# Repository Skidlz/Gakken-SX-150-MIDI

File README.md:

This project adds MIDI support to the Gakken SX-150 mk II using an Arduino R4.

This includes CCs for all original controls, plus additional parameters.

## Additional Hardware Features:
- Sustain and Release Stages (for existing hardware envelope)
- Inverted Envelope Mode
- Pulse, Dual Pulse, Super Saw, and other Waveforms
- Pulse Width Modulation
- Square and Triangle Sub Oscillators
- VCF Drive adjustment
- Envelope to VCF Depth Adjustment
- High Pass Filter Mode
- LFO to VCF Modulation
- Improved LFO sync
- VCA
- LED indicators for LFO and Envelope

## Additional Software Features:
 - Extra Software Envelopes with S/H
 - Extra Software LFOs
 - Pitch Bend
 - Portamento
 - Legato
 - Velocity-triggered Accent
 - Velocity Modulation
 - VCF Keytracking
 - Delay and Fade-in for Hardware LFO
 - Quantizing for Touchstrip

## Routing Diagram

## Schematic Diagram

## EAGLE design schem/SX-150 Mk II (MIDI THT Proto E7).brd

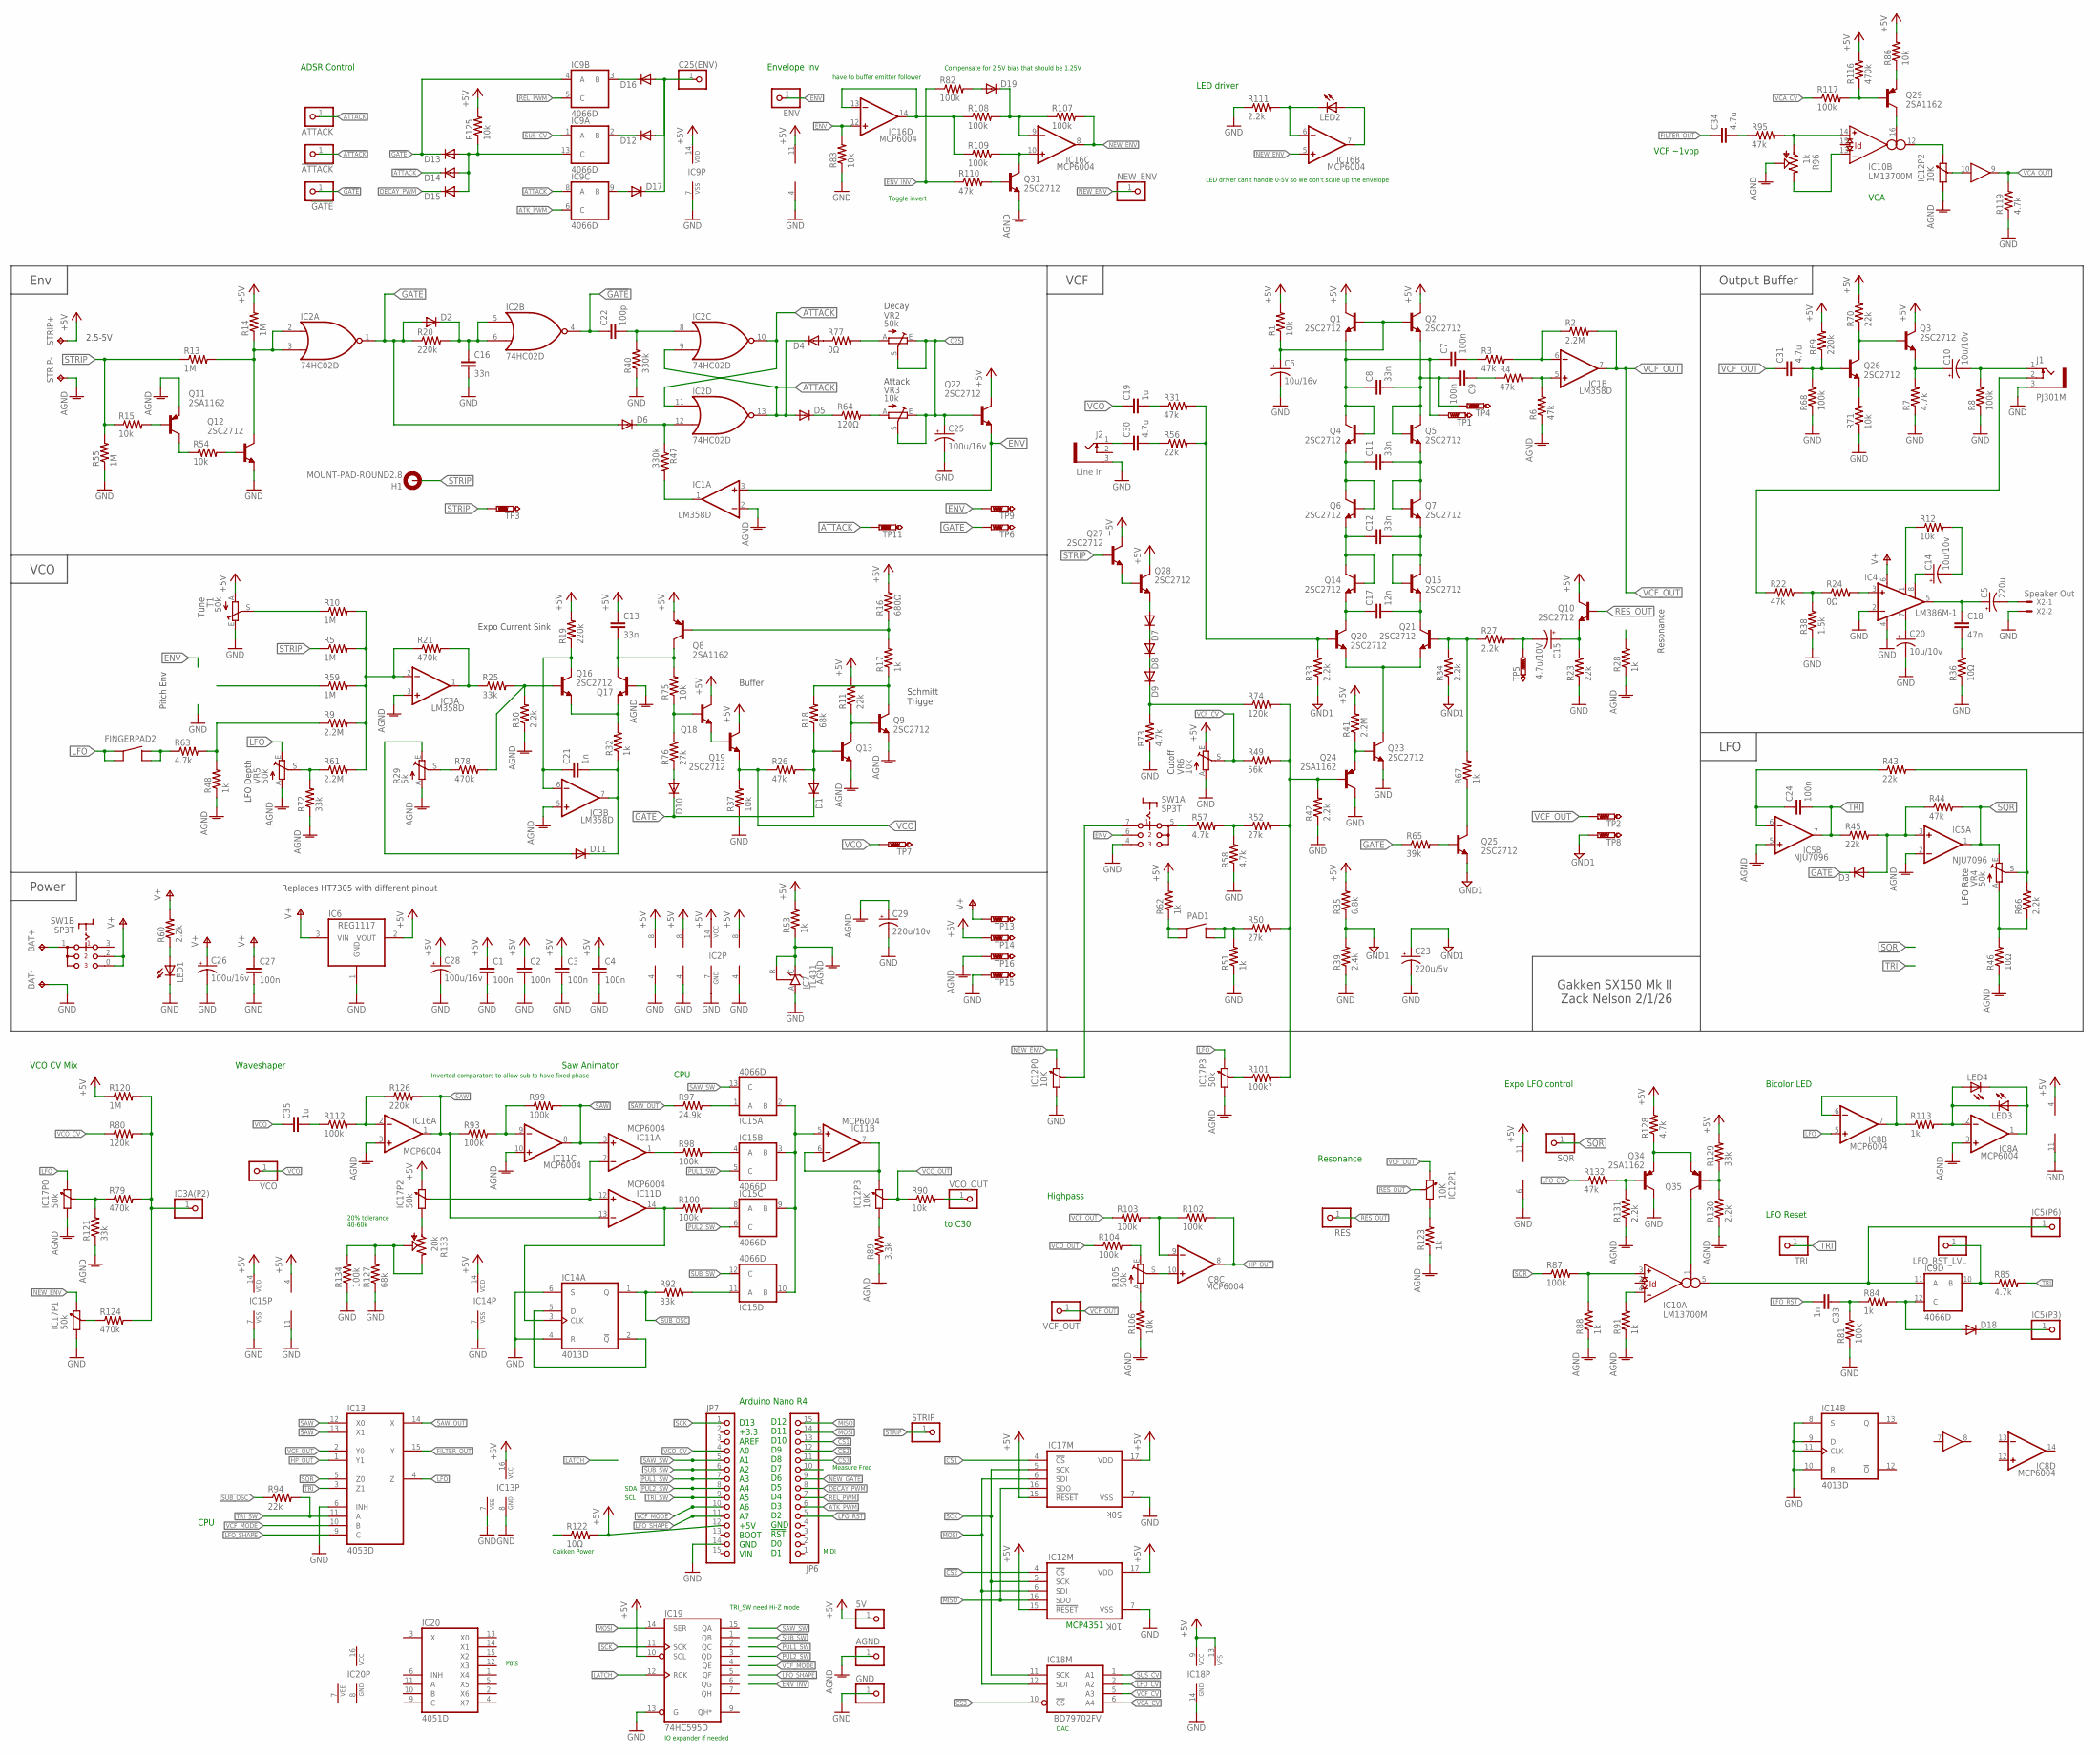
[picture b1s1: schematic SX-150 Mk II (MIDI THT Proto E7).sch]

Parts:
5V: PINHD-1X1; 1X01
!ATTACK: PINHD-1X1; 1X01
!GATE: PINHD-1X1; 1X01
AGND: PINHD-1X1; 1X01
ATTACK: PINHD-1X1; 1X01
BAT+: TPPAD1-13; P1-13
BAT-: TPPAD1-13; P1-13
C1, C2, C3, C4, C7, C9, C24, C27: 100n; C0603
C5: 220u; E2,5-6
C6: 10u/16v; E2,5-6
C8, C11, C12, C13, C16: 33n; C0603
C10, C14, C20: 10u/10v; E2,5-6
C15: 4.7u/10V; E2,5-6
C17: 12n; C0603
C18: 47n; C0603
C19, C35: 1u; C0603
C21, C33: 1n; C0603
C22: 100p; C0603
C23: 220u/5v; E2,5-6
C25, C26, C28: 100u/16v; E2,5-6
C25(ENV): PINHD-1X1; 1X01
C29: 220u/10v; E2,5-6
C30, C31, C34: 4.7u; C0603
D1, D10, D11: DIODE-DO41-7.6; DO41-7.6
D2, D3, D4, D5, D6, D7, D8, D9, D12, D13, D14, D15, D16, D17, D18, D19: DIODE-MINIMELF; MINIMELF
ENV: PINHD-1X1; 1X01
FINGERPAD2: GAKKEN-PAD
GND: PINHD-1X1; 1X01
H1: MOUNT-PAD-ROUND2.8; 2,8-PAD
IC1, IC3: LM358D; SO08
IC2: 74HC02D; SO14
IC3A(P2), IC5(P3), IC5(P6): PINHD-1X1; 1X01
IC4: LM386M-1; SO08
IC5: NJU7096; SO08
IC6: REG1117; SOT223
IC7: TL431; TO92-CLP
IC8, IC11, IC16: MCP6004; SO14
IC9, IC15: 4066D; SO14
IC10: LM13700M; SO16
IC12: 10K; TSSOP20_MC_MCH
IC13: 4053D; SO16
IC14: 4013D; SO14
IC17: 50k; TSSOP20_MC_MCH
IC18: BD79702FV; TSSOP14
IC19: 74HC595D; SO16
IC20: 4051D; SO16
J1: PJ301M; JACK-3.5-NOHOLE
J2: Line In; JACK-3.5-NOHOLE
JP6, JP7: PINHD-1X15; 1X15
LED1, LED2, LED3, LED4: LED3MM
LFO_RST_LVL: PINHD-1X1; 1X01
NEW_ENV: PINHD-1X1; 1X01
PAD1: GAKKEN-PAD
Q1, Q2, Q3, Q4, Q5, Q6, Q7, Q9, Q10, Q12, Q13, Q14, Q15, Q16, Q17, Q18, Q19, Q20, Q21, Q22, Q23, Q25, Q26, Q27, Q28, Q31: 2SC2712; SOT23-BEC
Q8, Q11, Q24, Q29, Q34, Q35: 2SA1162; SOT23-BEC
R1, R12, R15, R37, R54, R71, R75, R83, R86, R90, R106, R125: 10k; R0603
R2, R9, R41, R61: 2.2M; R0603
R3, R4, R6, R22, R26, R31, R44, R95, R110, R132: 47k; R0603
R5, R10, R13, R14, R55, R59, R120: 1M; R0603
R7, R57, R58, R63, R73, R85, R119, R128: 4.7k; R0603
R8, R68, R81, R82, R87, R93, R98, R99, R100, R102, R103, R104, R107, R108, R109, R112, R117, R134: 100k; R0603
R11, R23, R43, R45, R56, R70, R94: 22k; R0603
R16: 680Ω; R0603
R17, R28, R32, R48, R51, R53, R62, R67, R84, R88, R91, R113, R123: 1k; R0603
R18, R127: 68k; R0603
R19, R20, R69, R126: 220k; R0603
R21, R78, R79, R116, R124: 470k; R0603
R24, R77: 0Ω; R0603
R25, R72, R92, R121, R129: 33k; R0603
R27, R30, R33, R34, R42, R60, R66, R111, R130, R131: 2.2k; R0603
R29: 5k; B25P
R35: 6.8k; R0603
R36, R46, R122: 10Ω; R0603
R38: 1.5k; R0603
R39: 2.4k; R0603
R40, R47: 330k; R0603
R49: 56k; R0603
R50, R52, R76: 27k; R0603
R64: 120Ω; R0603
R65: 39k; R0603
R74, R80: 120k; R0603
R89: 3.3k; R0603
R96: 1k; B25P
R97: 24.9k; R0603
R101: 100k?; R0603
R105: 50k; B25P
R133: 20k; B25P
RES: PINHD-1X1; 1X01
SQR: PINHD-1X1; 1X01
STRIP: PINHD-1X1; 1X01
STRIP+: TPB2,54; B2,54
STRIP-: TPB2,54; B2,54
SW1: SP3T
T1: 50k; CA9V
TP1, TP2, TP3, TP4, TP5, TP6, TP7, TP8, TP9, TP11, TP13, TP14, TP15, TP16: PTR1B1,27; B1,27
TRI: PINHD-1X1; 1X01
VCF_OUT: PINHD-1X1; 1X01
VCO: PINHD-1X1; 1X01
VCO_OUT: PINHD-1X1; 1X01
VR2, VR4, VR5: 50k; CA9V
VR3, VR6: 10k; CA9V
X2: Speaker Out; 22-23-2021

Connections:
!ATTACK: !ATTACK.1, D14.C, IC2.10 (O), IC2.11 (I0)
!CS1: IC17.4 (!CS), JP6.13
!CS2: IC12.4 (!CS), JP6.12
!CS3: IC18.10 (!CS), JP6.11
!GATE: !GATE.1, C22.1, D1.C, D3.C, D10.C, D13.C, IC2.4 (O), IC9.4 (A)
!SAW: IC11.3 (+IN), IC11.8 (OUT), IC13.13 (X1), R99.2
+5V: 5V.1, C1.1, C2.1, C3.1, C4.1, C13.1, C28.+, IC1.8 (V+), IC2.14 (VCC), IC3.8 (V+), IC5.8 (V+), IC6.2 (VOUT), IC8.4 (V+), IC9.14 (VDD), IC10.11 (V+), IC11.4 (V+), IC12.15 (!RESET), IC12.17 (VDD), IC13.16 (VCC), IC14.14 (VDD), IC15.14 (VDD), IC16.11 (V-), IC17.15 (!RESET), IC17.17 (VDD), IC17.18 (B), IC18.9 (VCC), IC18.13 (VFS), IC19.10 (SCL), JP7.12, Q1.C, Q2.C, Q3.C, Q8.E, Q10.C, Q18.C, Q19.C, Q22.C, Q27.C, Q28.C, R1.2, R11.2, R14.2, R16.2, R19.2, R35.2, R41.2, R53.2, R62.2, R69.2, R70.2, R86.2, R116.2, R120.1, R122.2, R125.2, R128.2, R129.2, STRIP+.TP, T1.A, TP14.TP, VR6.E
AGND: AGND.1, C29.+, IC1.2 (-IN), IC3.3 (+IN), IC3.5 (+IN), IC5.2 (-IN), IC5.5 (+IN), IC7.C, IC7.R, IC8.3 (+IN), IC11.10 (+IN), IC12.20 (A), IC16.3 (+IN), IC17.1 (A), IC17.11 (A), Q9.E, Q11.E, Q13.E, Q17.B, Q31.E, R6.1, R28.1, R29.A, R30.1, R46.1, R48.1, R53.1, R72.1, R88.1, R89.1, R91.1, R96.S, R106.1, R121.1, R123.1, R130.1, R131.1, STRIP-.TP, TP16.TP, VR5.A
ATK_PWM: IC9.6 (C), JP6.6
ATTACK: ATTACK.1, D4.C, D5.A, IC2.9 (I1), IC2.13 (O), IC9.8 (A), TP11.TP
C25: C25.+, C25(ENV).1, D12.A, D16.A, D17.C, Q22.B, VR2.E, VR2.S, VR3.E, VR3.S
DECAY_PWM: D15.C, JP6.8
ENV: ENV.1, IC1.3 (+IN), IC16.12 (+IN), Q22.E, R83.2, SW1.6 (T2), TP9.TP
ENV_INV: R82.1, R110.1
FILTER_OUT: C34.1, IC13.15 (Y)
GATE: D2.A, D6.A, IC2.1 (O), R20.1, R65.1, TP6.TP
GND: BAT-.TP, C1.2, C2.2, C3.2, C4.2, C6.-, C16.2, C20.-, C23.-, C25.-, C26.-, C27.2, C28.-, C29.-, GND.1, IC1.4 (V-), IC2.7 (GND), IC3.4 (V-), IC4.2 (-IN), IC4.4 (GND), IC5.4 (V-), IC6.1 (GND), IC7.A, IC8.11 (V-), IC9.7 (VSS), IC10.6 (V-), IC11.11 (V-), IC12.7 (VSS), IC12.11 (A), IC13.6 (INH), IC13.7 (VEE), IC13.8 (GND), IC14.4 (R), IC14.6 (S), IC14.7 (VSS), IC14.8 (S), IC14.9 (D), IC14.10 (R), IC14.11 (CLK), IC15.7 (VSS), IC16.4 (V+), IC17.7 (VSS), IC17.10 (A), IC18.14 (GND), IC19.8 (GND), IC19.13 (G), IC20.8 (GND), J1.3 (1), J2.3 (1), JP7.14, LED1.K (C), Q12.E, Q23.E, Q24.C, Q34.C, R7.1, R8.1, R23.1, R36.1, R37.1, R38.1, R39.1, R40.1, R42.1, R51.1, R55.1, R58.1, R68.1, R71.1, R73.1, R81.1, R83.1, R111.1, R119.1, R127.1, R134.1, SW1.4 (T3), T1.E, TP15.TP, VR6.A, X2.2
GND1: C23.+, Q25.E, R33.1, R34.1, R35.1, R39.2, TP8.TP
HP_OUT: IC8.8 (OUT), IC13.1 (Y1), R102.2
LATCH: IC19.12 (RCK)
LFO: FINGERPAD2.A0, FINGERPAD2.A1, IC8.5 (+IN), IC13.4 (Z), IC17.3 (B), IC17.13 (B), VR5.E
LFO_CV: IC18.2 (A2), R132.1
LFO_RST: C33.2, JP6.5
LFO_SHAPE: IC13.9 (C), JP7.11
MISO: IC12.16 (SDO), IC17.16 (SDO), JP6.15
MOSI: IC12.6 (SDI), IC17.6 (SDI), IC18.12 (SDI), IC19.14 (SER), JP6.14
unnamed: IC1.1 (OUT), R47.2
unnamed: D5.C, R64.1
unnamed: IC2.2 (I0), IC2.3 (I1), Q12.C, R13.2, R14.1
unnamed: D12.C, IC9.2 (B)
unnamed: C22.2, IC2.8 (I0), R40.2
unnamed: Q12.B, R54.2
unnamed: C16.1, D2.C, IC2.5 (I0), IC2.6 (I1), R20.2
unnamed: D6.C, IC2.12 (I1), R47.1
unnamed: D4.A, R77.1
unnamed: D17.A, IC9.9 (B)
unnamed: R64.2, VR3.A
unnamed: D19.A, R82.2
unnamed: Q11.C, R54.1
unnamed: Q11.B, R15.2
unnamed: R61.1, R72.2, VR5.S
unnamed: IC5(P6).1, IC9.11 (A), IC10.5 (OUT)
unnamed: IC3.2 (-IN), R5.2, R9.2, R10.2, R21.1, R59.2, R61.2
unnamed: D18.C, IC5(P3).1
unnamed: R46.2, R66.1, VR4.A
unnamed: R43.2, R66.2, VR4.S
unnamed: IC3.1 (OUT), R21.2, R25.1
unnamed: Q16.B, R25.2, R30.2, R78.2
unnamed: R9.1, R48.2, R63.2
unnamed: R10.1, T1.S
unnamed: C13.2, Q8.C, Q17.C, R75.2
unnamed: Q8.B, R16.1, R17.2
unnamed: C21.2, D11.C, IC3.7 (OUT), R32.1
unnamed: Q16.E, Q17.E, R32.2
unnamed: C21.1, IC3.6 (-IN), Q16.C, R19.1
unnamed: Q9.C, R17.1, R18.2
unnamed: Q18.B, R75.1, R76.2
unnamed: Q18.E, Q19.B
unnamed: BAT+.TP, SW1.1
unnamed: Q9.B, Q13.C, R11.1
unnamed: D1.A, Q13.B, R18.1, R26.2
unnamed: D10.A, R76.1
unnamed: C7.1, C8.1, Q1.E, Q4.B, Q4.C, TP1.TP
unnamed: C8.2, C9.2, Q2.E, Q5.B, Q5.C, TP4.TP
unnamed: C6.+, Q1.B, Q2.B, R1.1
unnamed: Q20.E, Q21.E, Q23.C
unnamed: C11.1, Q4.E, Q6.B, Q6.C
unnamed: C11.2, Q5.E, Q7.B, Q7.C
unnamed: Q20.B, R31.2, R33.2, R56.2
unnamed: C12.1, Q6.E, Q14.B, Q14.C
unnamed: C12.2, Q7.E, Q15.B, Q15.C
unnamed: C17.1, Q14.E, Q20.C
unnamed: C17.2, Q15.E, Q21.C
unnamed: Q21.B, R27.1, R34.2, R67.2
unnamed: C7.2, R3.1
unnamed: C9.1, R4.1
unnamed: IC1.6 (-IN), R2.1, R3.2
unnamed: IC1.5 (+IN), R4.2, R6.2
unnamed: Q23.B, Q24.E, R41.1
unnamed: Q25.C, R67.1
unnamed: Q25.B, R65.2
unnamed: C15.-, R27.2, TP5.TP
unnamed: C15.+, Q10.E, R23.2
unnamed: IC17.9 (W), R124.1
unnamed: Q29.E, R86.1
unnamed: Q24.B, R42.2, R49.2, R50.2, R52.2, R74.2, R101.2
unnamed: R57.1, SW1.5 (P1)
unnamed: C35.2, R112.1
unnamed: R52.1, R57.2, R58.2
unnamed: PAD1.B0, PAD1.B1, R50.1, R51.2
unnamed: C19.2, R31.1
unnamed: C30.2, R56.1
unnamed: C30.1, J2.1 (2)
unnamed: C31.2, Q26.B, R68.2, R69.1
unnamed: Q3.B, Q26.C, R70.1
unnamed: Q26.E, R71.2
unnamed: C10.+, Q3.E, R7.2
unnamed: C10.-, J1.1 (2), R8.2
unnamed: Q27.E, Q28.B
unnamed: PAD1.A0, PAD1.A1, R62.1
unnamed: D7.A, Q28.E
unnamed: D7.C, D8.A
unnamed: D8.C, D9.A
unnamed: D9.C, R73.2, R74.1
unnamed: FINGERPAD2.B0, FINGERPAD2.B1, R63.1
unnamed: C20.+, IC4.7 (BYPASS)
unnamed: C14.+, IC4.8 (GAIN)
unnamed: IC4.1 (GAIN), R12.1
unnamed: C14.-, R12.2
unnamed: C5.+, C18.1, IC4.5 (OUT)
unnamed: IC4.3 (+IN), R24.2
unnamed: C5.-, X2.1
unnamed: J1.2 (3), R22.1
unnamed: C18.2, R36.2
unnamed: D11.A, R29.E
unnamed: R22.2, R24.1, R38.2
unnamed: LED1.A, R60.1
unnamed: IC10.16 (IABC), Q29.C
unnamed: R29.S, R78.1
unnamed: D13.A, D14.A, D15.A, IC9.13 (C), R125.1
unnamed: C24.1, IC5.6 (-IN), R43.1
unnamed: D19.C, IC16.9 (-IN), R107.1, R108.2
unnamed: D16.C, IC9.3 (B)
unnamed: R77.2, VR2.A
unnamed: D18.A, IC9.12 (C), R84.2
unnamed: IC11.1 (OUT), R98.1
unnamed: IC8.10 (+IN), R105.S
unnamed: IC16.13 (-IN), IC16.14 (OUT), R108.1, R109.1
unnamed: C33.1, R81.2, R84.1
unnamed: IC14.2 (!Q), IC14.5 (D)
unnamed: IC12.12 (W), SW1.7 (T1)
unnamed: IC10.3 (+IN), R87.2, R88.2
unnamed: IC10.4 (-IN), R91.2
unnamed: IC15.1 (A), R97.2
unnamed: IC15.4 (A), R98.2
unnamed: IC15.8 (A), R100.2
unnamed: IC10.14 (+IN), R95.2, R96.A
unnamed: IC12.1 (A), R89.2
unnamed: IC9.10 (B), LFO_RST_LVL.1, R85.1
unnamed: IC11.5 (+IN), IC15.2 (B), IC15.3 (B), IC15.9 (B), IC15.10 (B)
unnamed: IC10.13 (-IN), R96.E
unnamed: IC15.11 (A), R92.2
unnamed: IC11.6 (-IN), IC11.7 (OUT), IC12.3 (B)
unnamed: IC11.9 (-IN), R93.2, R99.1
unnamed: IC11.14 (OUT), IC14.3 (CLK), R100.1
unnamed: C34.2, R95.1
unnamed: IC8.9 (-IN), R102.1, R103.2
unnamed: Q29.B, R116.1, R117.2
unnamed: R104.2, R105.E
unnamed: IC10.10 (IN), IC12.19 (W)
unnamed: R105.A, R106.2
unnamed: IC16.10 (+IN), Q31.C, R109.2
unnamed: IC17.20 (A), R133.A
unnamed: Q31.B, R110.2
unnamed: IC8.1 (OUT), LED3.A, LED4.K (C)
unnamed: R127.2, R133.E, R133.S, R134.2
unnamed: IC16.7 (OUT), LED2.A
unnamed: IC16.6 (-IN), LED2.K (C), R111.2
unnamed: IC8.2 (-IN), LED3.K (C), LED4.A, R113.2
unnamed: IC8.6 (-IN), IC8.7 (OUT), R113.1
unnamed: D3.A, IC5.3 (+IN), R44.1, R45.2
unnamed: IC17.2 (W), R101.1
unnamed: IC17.12 (W), R79.1, R121.2
unnamed: IC3A(P2).1, R79.2, R80.2, R120.2, R124.2
unnamed: IC10.12 (OUT), IC12.18 (B)
unnamed: IC12.10 (A), R123.2
unnamed: IC16.2 (-IN), R112.2, R126.1
unnamed: R90.2, VCO_OUT.1
unnamed: Q34.E, Q35.E, R128.1
unnamed: Q35.B, R129.1, R130.2
unnamed: Q34.B, R131.2, R132.2
unnamed: IC10.1 (IABC), Q35.C
NEW_ENV: IC12.13 (B), IC16.5 (+IN), IC16.8 (OUT), IC17.8 (B), NEW_ENV.1, R107.2
NEW_GATE: JP6.9
PUL1_SW: IC15.5 (C), JP7.7
PUL2_SW: IC15.6 (C), JP7.8
REL_PWM: IC9.5 (C), JP6.7
RES_OUT: IC12.9 (W), Q10.B, RES.1
SAW: IC11.13 (-IN), IC13.12 (X0), IC16.1 (OUT), R93.1, R126.2
SAW_CV: IC11.2 (-IN), IC11.12 (+IN), IC17.19 (W)
SAW_OUT: IC13.14 (X), R97.1
SAW_SW: IC15.13 (C), JP7.5
SCK: IC12.5 (SCK), IC17.5 (SCK), IC18.11 (SCK), IC19.11 (SCK), JP7.1
SQR: IC5.1 (OUT), IC13.5 (Z0), R44.2, R87.1, SQR.1, VR4.E
STRIP: H1.B2,8, Q27.B, R5.1, R13.1, R15.1, R55.2, STRIP.1, TP3.TP
SUB_OSC: IC14.1 (Q), R92.1, R94.1
SUB_SW: IC15.12 (C), JP7.6
SUS_CV: IC9.1 (A), IC18.1 (A1)
TRI: C24.2, IC5.7 (OUT), IC13.3 (Z1), R45.1, R85.2, TRI.1
TRI_SW: IC13.11 (A), JP7.9, R94.2
V+: C26.+, C27.1, IC4.6 (VS), IC6.3 (VIN), R60.2, SW1.0 (T3), SW1.2 (T2), TP13.TP
VCA_CV: IC18.6 (A4), R117.1
VCA_OUT: IC10.9 (OUT), R119.2
VCC: IC19.16 (VCC), IC20.16 (VCC)
VCF_CV: IC18.5 (A3), R49.1, VR6.S
VCF_MODE: IC13.10 (B), JP7.10
VCF_OUT: C31.1, IC1.7 (OUT), IC12.8 (B), IC13.2 (Y0), R2.2, R103.1, TP2.TP, VCF_OUT.1
VCO: C19.1, C35.1, Q19.E, R26.1, R37.2, TP7.TP, VCO.1
VCO_CV: JP7.4, R80.1
VCO_OUT: IC12.2 (W), R90.1, R104.1
VEE: IC20.7 (VEE)

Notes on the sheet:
Decay
Attack
2.5-5V
LFO Rate
Expo Current Sink
Buffer
Schmitt Trigger
VCO
LFO Depth
Cutoff
Replaces HT7305 with different pinout
Env
VCF
LFO
Output Buffer
Power
Gakken SX150 Mk II Zack Nelson 2/1/26
Resonance
Pitch Env
Tune
LFO Reset
Expo LFO control
Saw Animator
CPU
Highpass
Bicolor LED
LED driver
VCF ~1vpp
MCP4351
VCA
D12 D11 D10 D9 D8 D7 D6 D5 D4 D3 D2 GND !RST D0 D1
D13 +3.3 AREF A0 A1 A2 A3 A4 A5 A6 A7 +5V BOOT GND VIN
Gakken Power
Measure Freq
to C30
MIDI
IO expander if needed
Inverted comparators to allow sub to have fixed phase
TRI_SW need Hi-Z mode
have to buffer emitter follower

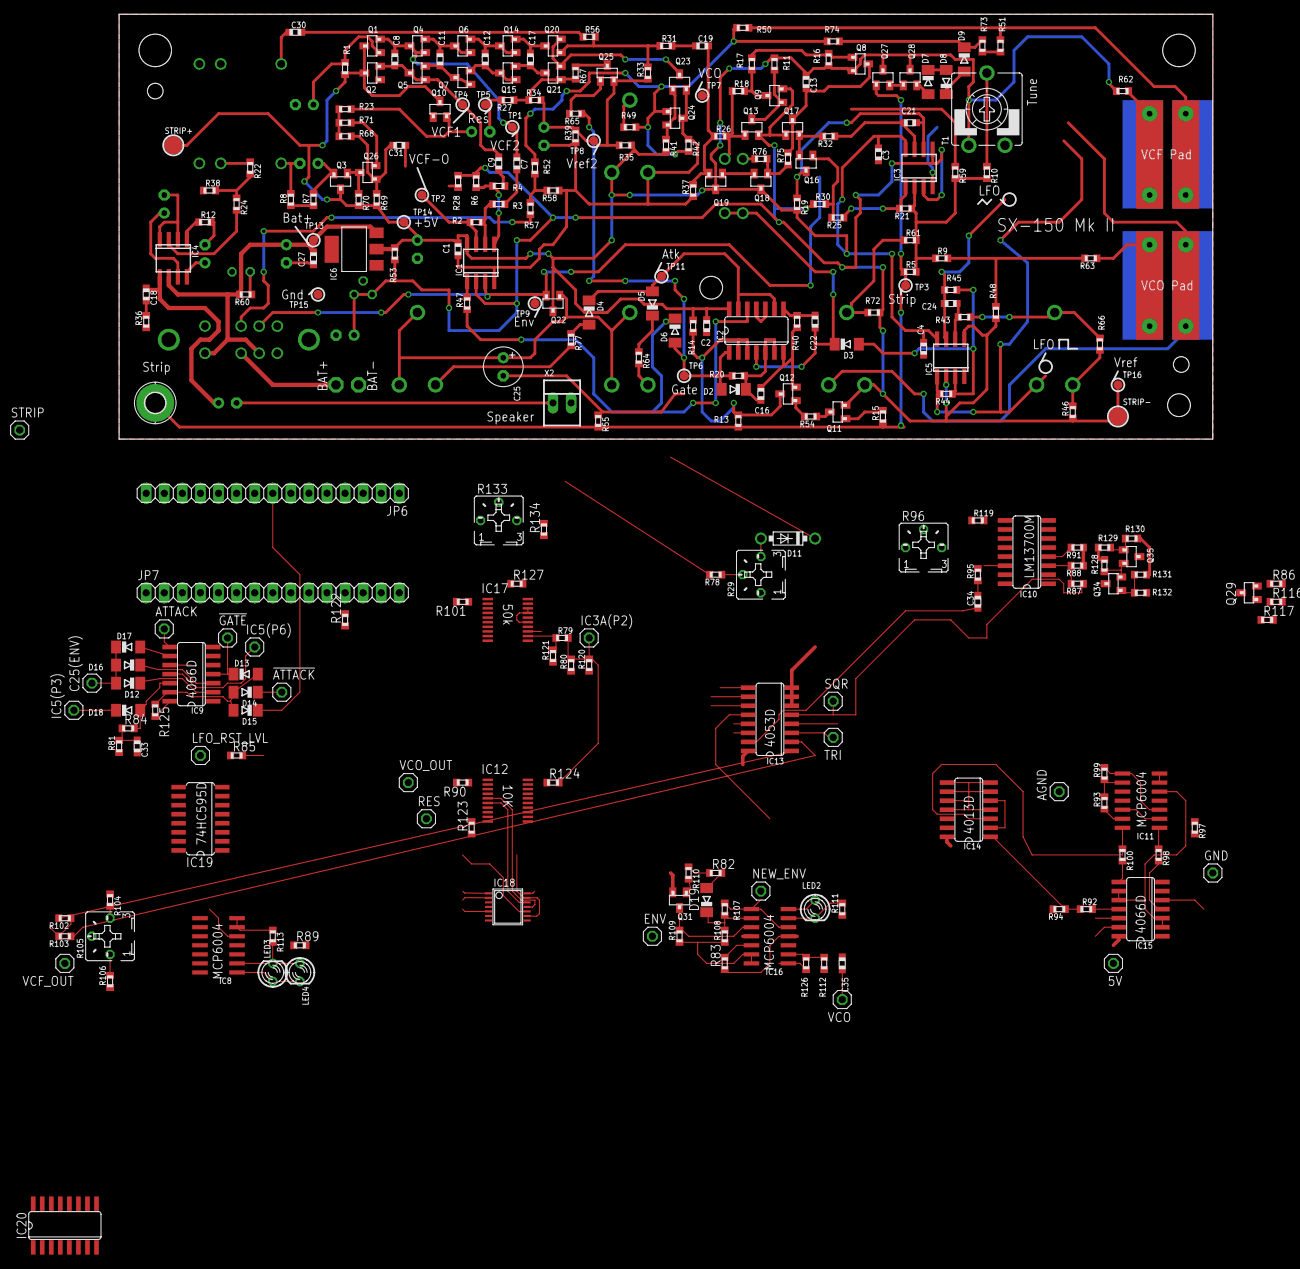
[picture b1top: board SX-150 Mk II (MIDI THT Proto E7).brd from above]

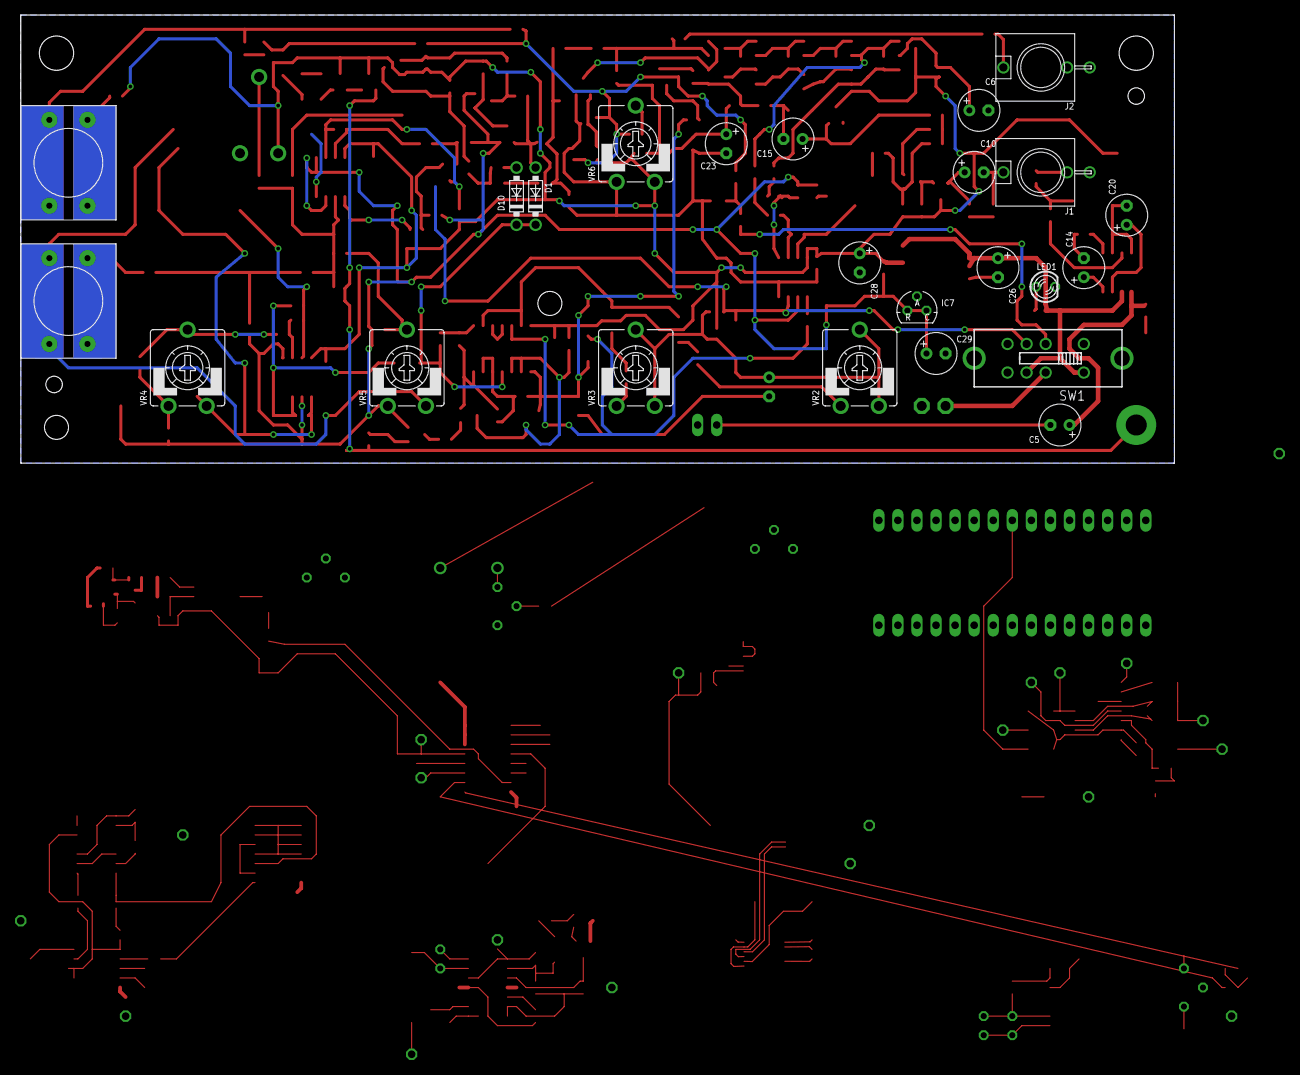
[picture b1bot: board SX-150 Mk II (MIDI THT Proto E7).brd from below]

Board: 2 copper layers, 153.7 x 59.7 mm, 293 parts (24 on the bottom side), 198 nets.

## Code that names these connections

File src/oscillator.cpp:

#include "oscillator.h"
#include <math.h>

//Library to control modified hardware oscillator in Gakken SX-150

Oscillator::Oscillator() {
    currentNote = 0;
    running = false;
    tuneScaling = 1.0;
    tuningOffset = 0;
    //setNote(12);

    for (uint8_t pin: { GATE_PIN, SAW_SW, SUB_SW, PUL1_SW, PUL2_SW, TRI_SW })
        pinMode(pin, OUTPUT); //init output pins
    setWaveform(SAW); //default to Saw
}

//toggles pins to pick waveform
void Oscillator::setWaveform(Waveform waveform) {
    _waveform = waveform;
    uint8_t config = waveformConfig[_waveform];

    digitalWrite(SAW_SW, !!(config & saw_b));
    digitalWrite(PUL1_SW, !!(config & pulse1_b));
    digitalWrite(PUL2_SW, !!(config & pulse2_b));
    digitalWrite(SUB_SW, !!(config & sub_b));

    if (config & tri_b) { //put in Hi-z mode to allow Triangle
        //CD4013 output toggles Saw polarity to make Triangle
        pinMode(TRI_SW, INPUT);
    } else { //force pin low to disable Triangle
        pinMode(TRI_SW, OUTPUT);
        digitalWrite(TRI_SW, (config & inv_saw_b) ? LOW : HIGH);
    }
}

//measures oscillator and sets tuning variabels to compensate
void Oscillator::calibrate() {
    Waveform waveformBackup = _waveform;
    setWaveform(NO_WAVE); //silence osc for calibration

    start(); //turn osc on
    setNote(C2); //play low note
    delay(100); //let it stabilize
    float lowResult = measureFreq();

    setNote(C5); //play high note
    delay(100); //let it stabilize
    float hiResult = measureFreq();
    stop(); //turn osc off

    setWaveform(waveformBackup); //restore original waveform

    //slope = rise over run: (y2 - y1) / (x2 - x1)
    tuneScaling = (hiResult - lowResult) / (C5 - C2);
    //find slope intercept (0V frequency): y = mx + b; b = y - mx
    tuningOffset = lowResult - (tuneScaling * (C2 - LOW_NOTE)) - LOW_NOTE;
}

void Oscillator::setNote(float note) {
    //truncate note range
    if (note >= LOW_NOTE) note -= LOW_NOTE;
    //if (note >= HIGH_NOTE) note = ((note - HIGH_NOTE) % 12) + (HIGH_NOTE - 12); //transpose to top octave

    uint16_t dacValue = ((note - tuningOffset) / tuneScaling) * (DAC_STEPS / NOTE_RANGE);
    if (dacValue > DAC_STEPS) dacValue = DAC_STEPS;

    analogWrite(A0, dacValue);
    currentNote = note;
}

void Oscillator::start() {
    digitalWrite(GATE_PIN, HIGH);
    running = true;
}

void Oscillator::stop() {
    digitalWrite(GATE_PIN, LOW);
    running = false;
}

float Oscillator::measureFreq() { //returns equiv MIDI note
    readingsIndex = 0;
    readingsComplete = false;

    //TODO: need to timeout if taking too long. try millis
    while(!readingsComplete); //wait for buffer to fill up with new readings

    float freq = getAvgFreq();

    float note = (12 * log2(freq / A4tuning)) + NOTE_A4; //convert from Hz to MIDI note #
    return note;
}

float Oscillator::getAvgFreq() {
    uint64_t averageReading = 0; //get average of all readings
    for (uint8_t i = 0; i < READINGS_MAX; i++) averageReading += readingsBuffer[i];
    averageReading /= READINGS_MAX;

    return (float)F_CPU/averageReading; //convert from timer count difference to frequency in Hz
}

//interrupt service routine for measuring Osc frequency
void Oscillator::captureISR() {
    static uint32_t lastTS = 0; //previous input capture reading
    static uint32_t currentTS = 0;

    lastTS = currentTS;
    currentTS = R_GPT0->GTCCR[0]; //read from input capture register
    lastDelta = currentTS - lastTS;

    readingsBuffer[readingsIndex++] = lastDelta;
    if (readingsIndex >= READINGS_MAX) {
        readingsComplete = true;
        readingsIndex %= READINGS_MAX; //wrap around at max
    }

    //clear interrupt flag for capture compare match A
    R_ICU->IELSR_b[IRQn_CCMPA].IR = 0;
}

void Oscillator::initTimer() { //hardware timer setup
    static bool timerInitialized = false;

    if (timerInitialized) return; //only run once regardless of osc count

    //Timer Setup------------------------------------------------------------------------------------
    R_MSTP->MSTPCRD_b.MSTPD5 = 0; //enable GPT0 module clock (General PWM Timer 321 to 320 Module Stop)
    delayMicroseconds(10);

    R_GPT0->GTCR_b.CST = 0; //stop timer
    R_GPT0->GTCR_b.MD = 0b000; //saw-wave PWM mode (000b)

    R_GPT0->GTUDDTYC = 0b11; //set 11b first (per datasheet Figure 22.17)
    R_GPT0->GTUDDTYC = 0b01; //01b for up-counting

    //R_GPT0->GTCR_b.TPCS = 0b011; //PCLKD/64 prescale
    R_GPT0->GTPR = 0xFFFFFFFF; //max cycle
    R_GPT0->GTCNT = 0; //0 initial count

    //GTCCRA input capture enabled on the...
    R_GPT0->GTICASR_b.ASCARBL = 1; //rising edge of GTIOCA input when GTIOCB input is 0
    R_GPT0->GTICASR_b.ASCARBH = 1; //rising edge of GTIOCA input when GTIOCB input is 1

    R_GPT0->GTCR_b.CST = 1; //start count operation

    //GPIO Pin D7 (P107) Setup-----------------------------------------------------------------------
    R_PFS->PORT[1].PIN[7].PmnPFS_b.PMR = 1; //Used as an I/O port for peripheral functions
    R_PFS->PORT[1].PIN[7].PmnPFS_b.PSEL = 0b11; //GTIOC0A (GPT peripheral function)

    //Interrupt Setup--------------------------------------------------------------------------------
    //assign GPT0 Capture to IRQn_CCMPA (AGT0_INT_IRQn #17)
    R_ICU->IELSR_b[IRQn_CCMPA].IELS = ELC_EVENT_GPT0_CAPTURE_COMPARE_A;
    NVIC_SetVector(IRQn_CCMPA, (uint32_t)&Oscillator::captureISR); //point to the ISR function
    NVIC_SetPriority(IRQn_CCMPA, 12);
    NVIC_EnableIRQ(IRQn_CCMPA);

    //TODO: setup timer overflow interrupt?

    timerInitialized = true;
}

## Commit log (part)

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2026-05-28 Init WIP
2026-05-28 Remove README
2026-06-03 Adding child classes and configs for DACs and DigiPots Adding abstract "AnalogOutput" class
2026-06-03 Adding WIP Schems
2026-06-04 Moving glide and VCF into Voice
2026-06-05 Moving PWM modulators into Osc
2026-06-10 Moving CC functionality into Param structs
2026-06-11 Adding routing image
2026-06-12 Make Osc responsible for calling update and gate methods of Modulator members
    Adding S/H param
2026-06-14 Moving vcaADSR into Voice Adding ADSR Params
2026-06-15 Adding hw_lfo Adding params
2026-06-16 Adding params for HW_adsr
2026-06-17 Removing Osc start/stop() and running status
2026-06-18 Adding legato for hw_adsr and osc Testing note priority options
2026-06-19 Adding noise LFO waveform and slew setting
2026-06-20 Improving params for HW_LFO, and adding reset modes Moving functionality out of main into noteAssigner
2026-06-21 Adding EnumParams that convert from CC to enum values/string Adding modulation to Params Adding FloatParams that help handle new modulation and detect changes
2026-06-23 Adding Routes to route modulation
    Rename some classes for consistency
    Fix issue of redefined "output" for modulators
    Adding "SimpleParam" for non-modulated Params

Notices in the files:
parts and their libraries:
COPYRIGHT: Copyright (C) 2026 Ultra Librarian. All rights reserved.
